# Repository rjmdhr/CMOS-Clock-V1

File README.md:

# CMOS-Clock-V1
A 12-hour discrete logic CMOS clock which drives several displays through logic ICs clocked via an external crystal oscillator. You can view my write-up [here](https://github.com/rjmdhr/CMOS-Clock-V1/blob/main/Report.pdf).

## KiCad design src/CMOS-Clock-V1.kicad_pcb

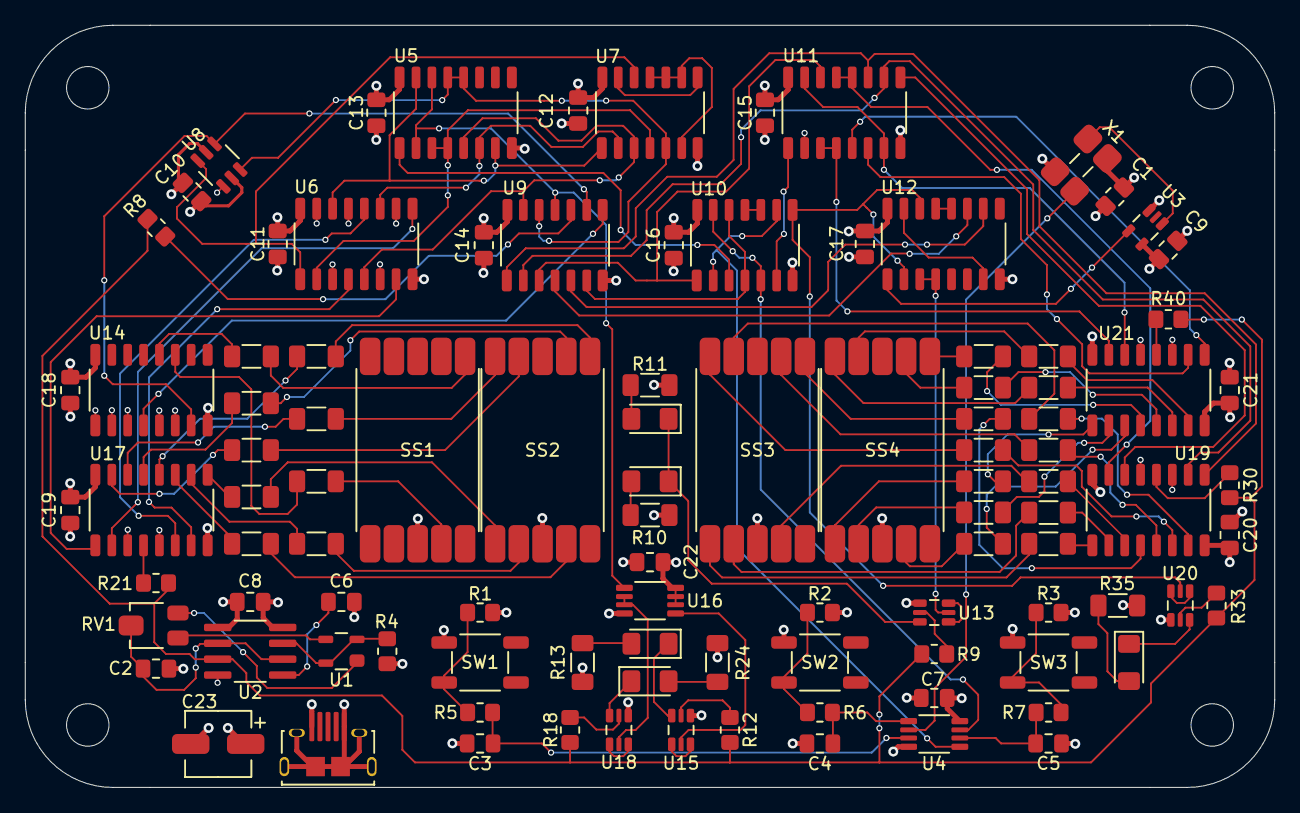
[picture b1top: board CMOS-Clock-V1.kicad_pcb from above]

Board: 4 copper layers, 100.0 x 61.0 mm, 102 parts (0 on the bottom side), 122 nets.

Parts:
C1: 10n; C_0805_2012Metric_Pad1.18x1.45mm_HandSolder
C2: 1n; C_0805_2012Metric_Pad1.18x1.45mm_HandSolder
C3, C4, C5: 1u; C_0805_2012Metric_Pad1.18x1.45mm_HandSolder
C6, C7, C8, C9, C10, C11, C12, C13, C14, C15, C16, C17, C18, C19, C20, C21, C22: 0.1u; C_0805_2012Metric_Pad1.18x1.45mm_HandSolder
C23: 100u; 865080142007
D1, D2, D5: Red; LED_1206_3216Metric_Pad1.42x1.75mm_HandSolder
D3: Amber; LED_1206_3216Metric_Pad1.42x1.75mm_HandSolder
D4: Violet; LED_1206_3216Metric_Pad1.42x1.75mm_HandSolder
J1: USB_B_Micro; AMPHENOL_10118194-0001LF
R1, R2, R3, R8, R9, R12, R18, R21, R30, R33, R40: 1.58k; R_0805_2012Metric_Pad1.20x1.40mm_HandSolder
R4: 1k; R_0805_2012Metric_Pad1.20x1.40mm_HandSolder
R5, R6, R7: 7.5k; R_0805_2012Metric_Pad1.20x1.40mm_HandSolder
R10, R11, R13, R35: 143; R_1206_3216Metric_Pad1.30x1.75mm_HandSolder
R14, R15, R16, R17, R19, R20, R22, R23, R24, R25, R26, R27, R28, R29, R31, R32, R34, R36, R37, R38, R39, R41, R42, R43: 84.5; R_1206_3216Metric_Pad1.30x1.75mm_HandSolder
RV1: 1M; TRIM_TC33X-2-105E
SS1, SS2, SS3: VDMR10C0
SS4: VDMYR0C0; VDMR10C0
SW1, SW2, SW3: SW_Push; PTS 647 SK38 SMTR2 LFS
U1: BAS28,215; SOT143(B)
U2: 7555; ICM7555
U3: 74AHC1G4215
U4: 74AHC3G14DP,125; SOT505-2
U5, U11, U12: 74HC390D,652; SOT109-1
U6: 74AHC157D,118; SOT109-1
U7: 74HC27D,653; SOT108-1
U8: 74LVC1G157; SOT457
U9: 74AHC08D,118; SOT108-1
U10: 74AHC86D,118; SOT108-1
U13, U15, U18, U20: 2N7002PS; SOT363
U14, U17, U19, U21: MC14511BDR2G; SOT109-1
U16: 74LVC1G74DP,125; SOT505-2
X1: OM-7604-C7; OSC_OM-7604-C7

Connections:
0Blank: U9.8, U14.4
GND: C1.2, C2.2, C3.2, C4.2, C5.2, C6.2, C7.2, C8.2, C9.2, C10.2, C11.2, C12.2, C13.2, C14.2, C15.2, C16.2, C17.2, C18.2, C19.2, C20.2, C21.2, C22.2, C23.2, J1.5, J1.6, R1.2, R2.2, R3.2, SS1.3, SS2.3, SS3.3, SS4.3, U2.1, U3.3, U4.4, U5.8, U6.3, U6.8, U6.10, U6.13, U6.15, U7.7, U8.2, U9.7, U10.7, U11.2, U11.8, U12.8, U13.1, U14.1, U14.2, U14.5, U14.6, U14.8, U15.1, U16.4, U17.5, U17.8, U18.1, U19.5, U19.8, U20.1, U21.5, U21.8, X1.2
unnamed: C2.1, RV1.2, U2.2, U2.6
unnamed: C3.1, R5.2, U4.3
unnamed: C4.1, R6.2, U4.1
unnamed: C5.1, R7.2, U4.6
unnamed: C6.1, U2.5
unnamed: D1.1, D2.1, U13.3
unnamed: D1.2, R11.2
unnamed: D2.2, R10.2
unnamed: D3.1, U15.3
unnamed: D3.2, R13.2
unnamed: D4.1, U18.3
unnamed: D4.2, R24.2
unnamed: D5.1, U20.3
unnamed: D5.2, R35.2
unnamed: R1.1, R5.1, SW1.2
unnamed: R2.1, R6.1, SW2.2
unnamed: R3.1, R7.1, SW3.2
unnamed: R4.2, U1.2, U1.4, U2.7
unnamed: R8.2, U9.10
unnamed: R9.2, U13.2
unnamed: R12.2, U15.2
unnamed: R14.1, SS1.4
unnamed: R14.2, U14.11
unnamed: R15.1, U14.12
unnamed: R15.2, SS1.6
unnamed: R16.1, U17.14
unnamed: R16.2, SS2.10
unnamed: R17.1, SS2.1
unnamed: R17.2, U17.9
unnamed: R18.2, U18.2
unnamed: R19.1, U17.15
unnamed: R19.2, SS2.9
unnamed: R20.1, SS2.2
unnamed: R20.2, U17.10
unnamed: R21.2, U17.4
unnamed: R22.1, U17.13
unnamed: R22.2, SS2.7
unnamed: R23.1, SS2.4
unnamed: R23.2, U17.11
unnamed: R25.1, U17.12
unnamed: R25.2, SS2.6
unnamed: R26.1, U19.14
unnamed: R26.2, SS3.10
unnamed: R27.1, SS3.1
unnamed: R27.2, U19.9
unnamed: R28.1, U19.15
unnamed: R28.2, SS3.9
unnamed: R29.1, SS3.2
unnamed: R29.2, U19.10
unnamed: R30.2, U19.4
unnamed: R31.1, U19.13
unnamed: R31.2, SS3.7
unnamed: R32.1, SS3.4
unnamed: R32.2, U19.11
unnamed: R33.2, U20.2
unnamed: R34.1, U19.12
unnamed: R34.2, SS3.6
unnamed: R36.1, U21.14
unnamed: R36.2, SS4.10
unnamed: R37.1, SS4.1
unnamed: R37.2, U21.9
unnamed: R38.1, U21.15
unnamed: R38.2, SS4.9
unnamed: R39.1, SS4.2
unnamed: R39.2, U21.10
unnamed: R40.2, U21.4
unnamed: R41.1, U21.13
unnamed: R41.2, SS4.7
unnamed: R42.1, SS4.4
unnamed: R42.2, U21.11
unnamed: R43.1, U21.12
unnamed: R43.2, SS4.6
unnamed: RV1.1, U1.3
unnamed: RV1.3, U1.1
unnamed: U3.1, X1.1
unnamed: U6.1, U7.12, U8.6
unnamed: U7.6, U7.9, U7.10, U7.11
unnamed: U7.8, U7.13
unnamed: U9.3, U10.1, U11.14
unnamed: U5.1, U10.3
unnamed: U10.6, U11.1
unnamed: U10.10, U10.11
unnamed: U9.6, U10.4, U10.12
unnamed: U9.5, U12.10
unnamed: U9.4, U12.11
unnamed: U12.12, U12.13
unnamed: U12.7, U12.15
unnamed: U13.4, U13.6
unnamed: U15.4, U15.6
unnamed: U15.5, U16.5
unnamed: U16.2, U16.3, U18.5
unnamed: U18.4, U18.6
unnamed: U20.4, U20.6
VCC: C1.1, C7.1, C8.1, C9.1, C10.1, C11.1, C12.1, C13.1, C14.1, C15.1, C16.1, C17.1, C18.1, C19.1, C20.1, C21.1, C22.1, C23.1, J1.1, R4.1, R10.1, R11.1, R13.1, R24.1, R35.1, SW1.1, SW2.1, SW3.1, U2.4, U2.8, U3.5, U4.8, U5.16, U6.6, U6.16, U7.14, U8.1, U8.5, U9.14, U10.14, U11.16, U12.16, U14.3, U14.16, U16.6, U16.7, U16.8, U17.3, U17.16, U19.3, U19.16, U21.3, U21.16, X1.4
clk: U3.4, U12.1
clkoe: U4.2, X1.3
hr_set: U4.5, U10.2, U10.9
hrst: U5.2, U5.14, U9.11, U16.1
ih0Q0: U5.3, U5.4, U6.2, U7.4
ih0Q1: U5.5, U6.5, U7.3, U9.13
ih0Q2: U5.6, U6.11, U7.2
ih0Q3: U5.7, U5.15, U6.14, U7.1
ih1Q0: U5.12, U5.13, U7.5, U8.3, U9.12
min_set: U4.7, U10.5, U10.13
oh0Q0: U6.4, U17.7
oh0Q1: U6.7, U17.1
oh0Q2: U6.9, U17.2
oh0Q3: U6.12, U17.6
oh1Q0: U8.4, U9.9, U14.7
om0Q0: U11.3, U11.4, U21.7
om0Q1: U11.5, U21.1
om0Q2: U11.6, U21.2
om0Q3: U11.7, U11.15, U21.6
om1Q0: U11.12, U11.13, U19.7
om1Q1: U9.1, U11.11, U19.1
om1Q2: U9.2, U11.10, U19.2
om1Q3: U11.9, U19.6
os0Q0: U12.3, U12.4, U13.5
pwm: R8.1, R9.1, R12.1, R18.1, R21.1, R30.1, R33.1, R40.1, U2.3
srst: U10.8, U12.2, U12.14, U20.5

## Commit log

2021-07-13 Project
2021-08-05 Finish Schematic
2021-10-01 Files
2021-10-01 Logisim files
2023-01-10 Add report
